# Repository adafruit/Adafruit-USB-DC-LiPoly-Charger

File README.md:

# PCB for the Adafruit USB/DC Lithium Ion/Polymer charger

This is the PCB for the Adafruit USB/DC Lithium Ion/Polymer charger
__Format is EagleCAD schematic and board layout__

Charge your single-cell lithium ion/polymer battery any which way you like with this board. Have a USB connection? No problem, just plug into the miniUSB connector. Only have a wall adapter? Any standard 2.1mm DC adapter which puts out 5 to 12VDC will work fine. If both are plugged in, the charger will automatically choose whichever has the highest voltage.

Other nice things about this charger include multiple LEDs for power & charging status, including a charging LED which will blink when the battery is full. If the charger gets too hot from high-speed charging, it will slow down the charge rate automatically. You can easily adjust the charge rate up to 1.2A or down to 100mA.

For use with Adafruit Lipoly/LiIon batteries only! Other batteries may have different voltage, chemistry, polarity or pinout.

- Use USB or DC power - 5 to 12V input
- Charges one single-cell 3.7/4.2v batteries (not for older 3.6/4.1v cells) with constant current/constant voltage
- Three indicator LEDs - green for Power, orange for charging and red for error
- Charging LED will blink when the battery is full
- You don't have to worry about heat dissipation in the charger, even when plugging in a 12V DC power jack - thermal protection inside will slow down the charge rate to prevent damage
- 2 JST connections so you can keep the battery plugged in and powering your project
- Terminal block connections galore (if you don't like JST connectors) just solder in 3.5mm terminal blocks
- Default charge rate is about 500mA, but you can easily change this by soldering in a through-hole resistor on. The chip can do 100-1200 mA charging
- Safety timer will stop charging after about 14 hours
- The chip supports a standard 10K thermistor, which we have stuffed as a standard resistor. You can solder in a thermistor easily
- [Lots of information in the datasheet for the MCP73861](http://www.microchip.com/wwwproducts/Devices.aspx?dDocName=en020210)
- Fully assembled, tested and comes with a free JST cable
- [Schematic available for your perusal](https://www.adafruit.com/datasheets/mcp73861.png)
- Dimensions: 1.75" x 1.6"

## License

Adafruit invests time and resources providing this open source design, 
please support Adafruit and open-source hardware by purchasing 
products from Adafruit!

Designed by Adafruit Industries.  
Creative Commons Attribution, Share-Alike license, check license.txt for more information
All text above must be included in any redistribution

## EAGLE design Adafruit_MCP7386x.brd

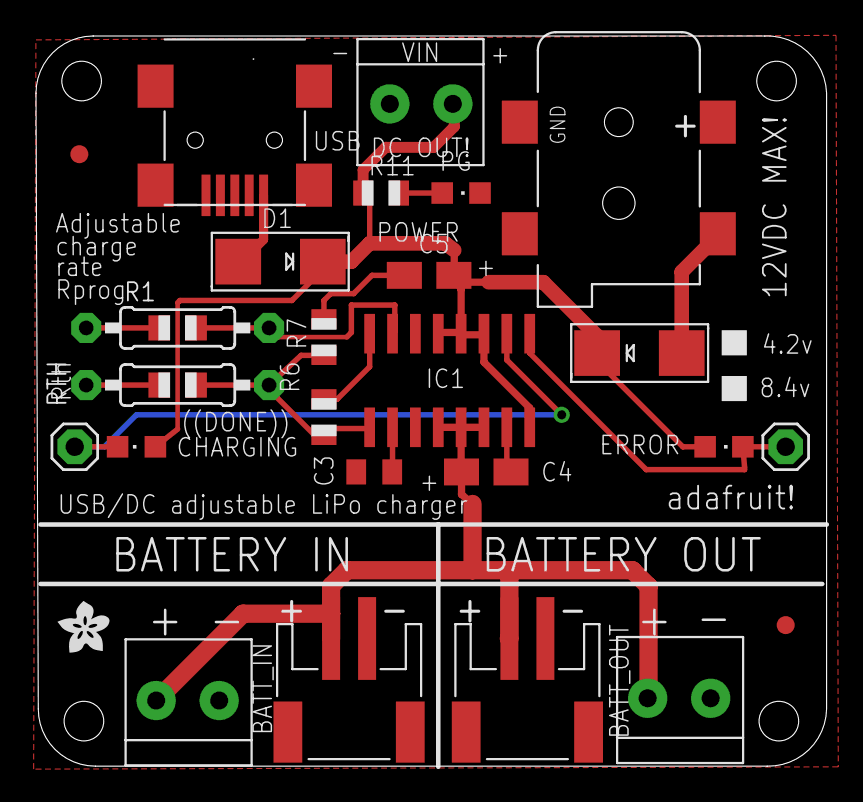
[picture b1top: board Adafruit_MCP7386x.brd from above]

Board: 2 copper layers, 43.9 x 40.6 mm, 26 parts (0 on the bottom side), 12 nets.

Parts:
BATT_IN: JSTPH2
BATT_OUT: JSTPH2
C3: 0.47uF; C0805K
C4, C5: 10uF; A/3216-18R
CHG: ORANGE; CHIPLED_0805
D1, D2: B120; SMADIODE
ERR: RED; CHIPLED_0805
IC1: SO16
IN: 1X2-3.5MM; 3.5MMTERM
OUT: 1X2-3.5MM; 3.5MMTERM
PG: GREEN; CHIPLED_0805
R1: adj; 0805-THM
R6: 6.19K; R0805
R7: 7.3k; R0805
R11: 470; R0805
RTH: 10K @ 25degC; 0805-THM
STAT3, STAT4: 1X01
U$1: 2.1MMJACKSMT; DCJACK_2MM_SMT
U$2: ADAFRUIT200MIL
U$3, U$4: FIDUCIAL; FIDUCIAL_1MM
USB: MINI-USB; USB-MINIB
VIN: 1X2-3.5MM; 3.5MMTERM

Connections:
BATT+: BATT_IN.2, BATT_OUT.2, C4.+, IC1.12, IC1.13, IC1.14, IN.2, OUT.2
GND: BATT_IN.1, BATT_OUT.1, C3.2, C4.-, C5.-, IC1.6, IC1.11, IC1.15, IN.1, OUT.1, PG.C, R1.1, R7.2, RTH.1, U$1.GND, U$1.GNDBREAK, USB.GND, VIN.1
unnamed: D1.A, USB.VBUS
unnamed: IC1.7, R1.2
unnamed: CHG.C, IC1.2, STAT3.1
unnamed: ERR.C, IC1.1, STAT4.1
unnamed: C3.1, IC1.10
unnamed: IC1.8, R6.2
unnamed: IC1.9, R6.1, R7.1, RTH.2
unnamed: PG.A, R11.2
unnamed: D2.A, U$1.PWR2
VCC: C5.+, CHG.A, D1.C, D2.C, ERR.A, IC1.3, IC1.4, IC1.5, IC1.16, R11.1, VIN.2

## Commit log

2013-08-06 12V max Lipo charger
2013-08-06 read
2019-04-25 readme + image
